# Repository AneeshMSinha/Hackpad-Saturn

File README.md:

# Hackpad-Saturn
My repository for Hack club, blueprint hackpad, called Saturn
This was an interesting and challenging project, was my first timee learning how to use Kicad and KMK.
## PCB
| Schematic | PCB |
|----------|----------|
|   | |
## Case

## Bill of materials

- 1 XIAO RP 2040 DIP
- 1 EC11 Rotary Encoder
- 1 SSD1306-0.91-OLED
- 1 PCB (black)
- 11 Cherry MX switches
- 11 Keycaps
- 12 DO-35 Diodes
- 1 3D printed case

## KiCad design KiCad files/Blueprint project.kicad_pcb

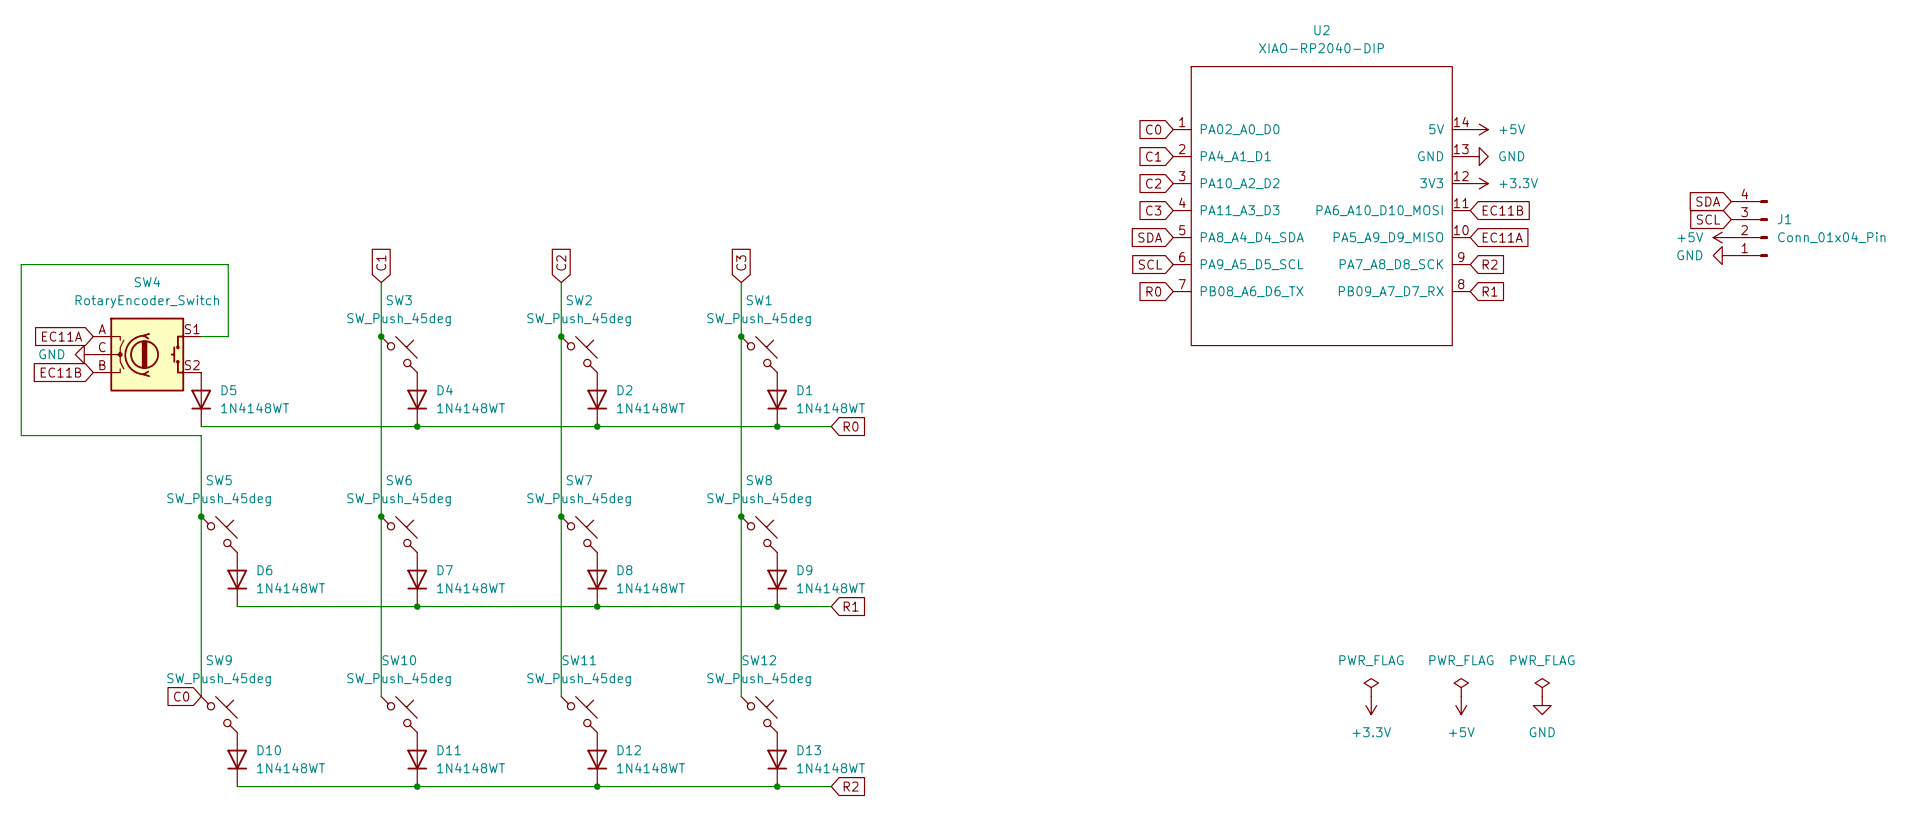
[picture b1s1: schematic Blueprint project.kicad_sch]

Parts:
D1, D2, D4, D5, D6, D7, D8, D9, D10, D11, D12, D13: 1N4148WT; D_DO-35_SOD27_P7.62mm_Horizontal
J1: Conn_01x04_Pin; SSD1306-0.91-OLED-4pin-128x32
SW1, SW2, SW3, SW5, SW6, SW7, SW8, SW9, SW10, SW11, SW12: SW_Push_45deg; SW_Cherry_MX_1.00u_PCB
SW4: RotaryEncoder_Switch; RotaryEncoder_Alps_EC11E-Switch_Vertical_H20mm
U2: XIAO-RP2040-DIP

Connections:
+3.3V: U2.12 (3V3)
+5V: J1.2, U2.14 (5V)
C0: SW4.S1, SW5.1, SW9.1, U2.1 (PA02_A0_D0)
C1: SW3.1, SW6.1, SW10.1, U2.2 (PA4_A1_D1)
C2: SW2.1, SW7.1, SW11.1, U2.3 (PA10_A2_D2)
C3: SW1.1, SW8.1, SW12.1, U2.4 (PA11_A3_D3)
EC11A: SW4.A, U2.10 (PA5_A9_D9_MISO)
EC11B: SW4.B, U2.11 (PA6_A10_D10_MOSI)
GND: J1.1, SW4.C, U2.13 (GND)
unnamed: D1.2 (A), SW1.2
unnamed: D2.2 (A), SW2.2
unnamed: D4.2 (A), SW3.2
unnamed: D5.2 (A), SW4.S2
unnamed: D6.2 (A), SW5.2
unnamed: D7.2 (A), SW6.2
unnamed: D8.2 (A), SW7.2
unnamed: D9.2 (A), SW8.2
unnamed: D10.2 (A), SW9.2
unnamed: D11.2 (A), SW10.2
unnamed: D12.2 (A), SW11.2
unnamed: D13.2 (A), SW12.2
R0: D1.1 (K), D2.1 (K), D4.1 (K), D5.1 (K), U2.7 (PB08_A6_D6_TX)
R1: D6.1 (K), D7.1 (K), D8.1 (K), D9.1 (K), U2.8 (PB09_A7_D7_RX)
R2: D10.1 (K), D11.1 (K), D12.1 (K), D13.1 (K), U2.9 (PA7_A8_D8_SCK)
SCL: J1.3, U2.6 (PA9_A5_D5_SCL)
SDA: J1.4, U2.5 (PA8_A4_D4_SDA)

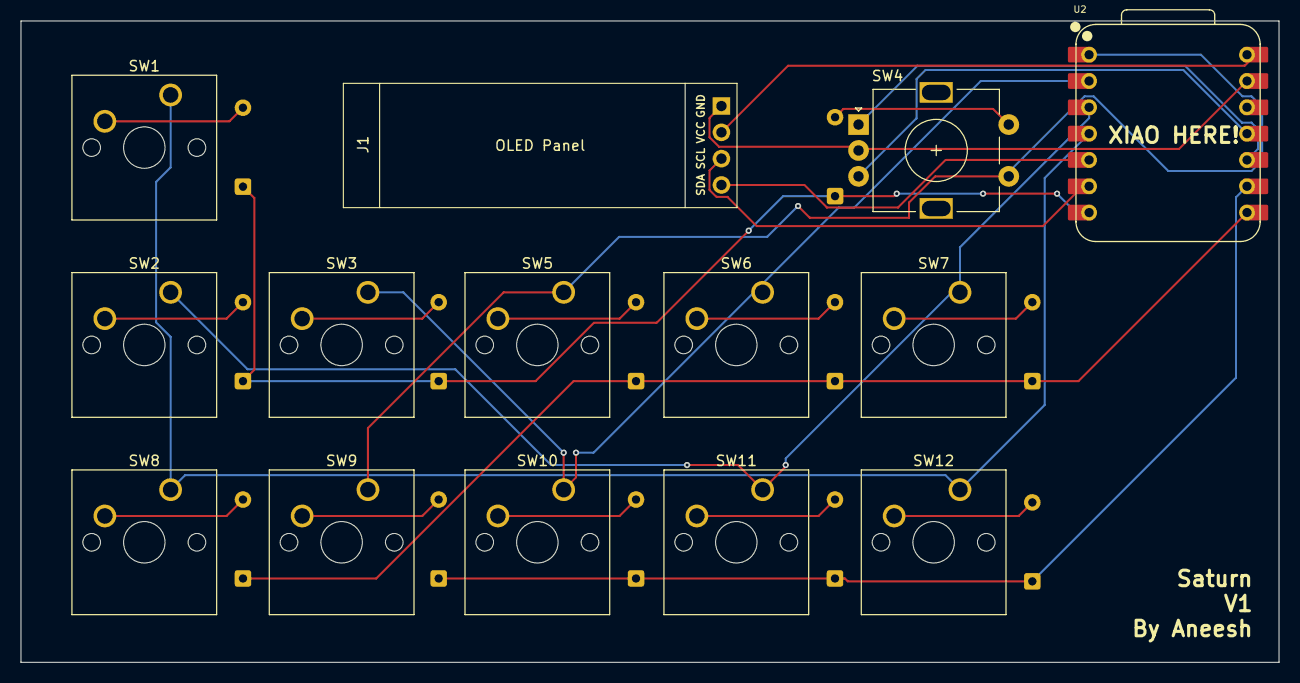
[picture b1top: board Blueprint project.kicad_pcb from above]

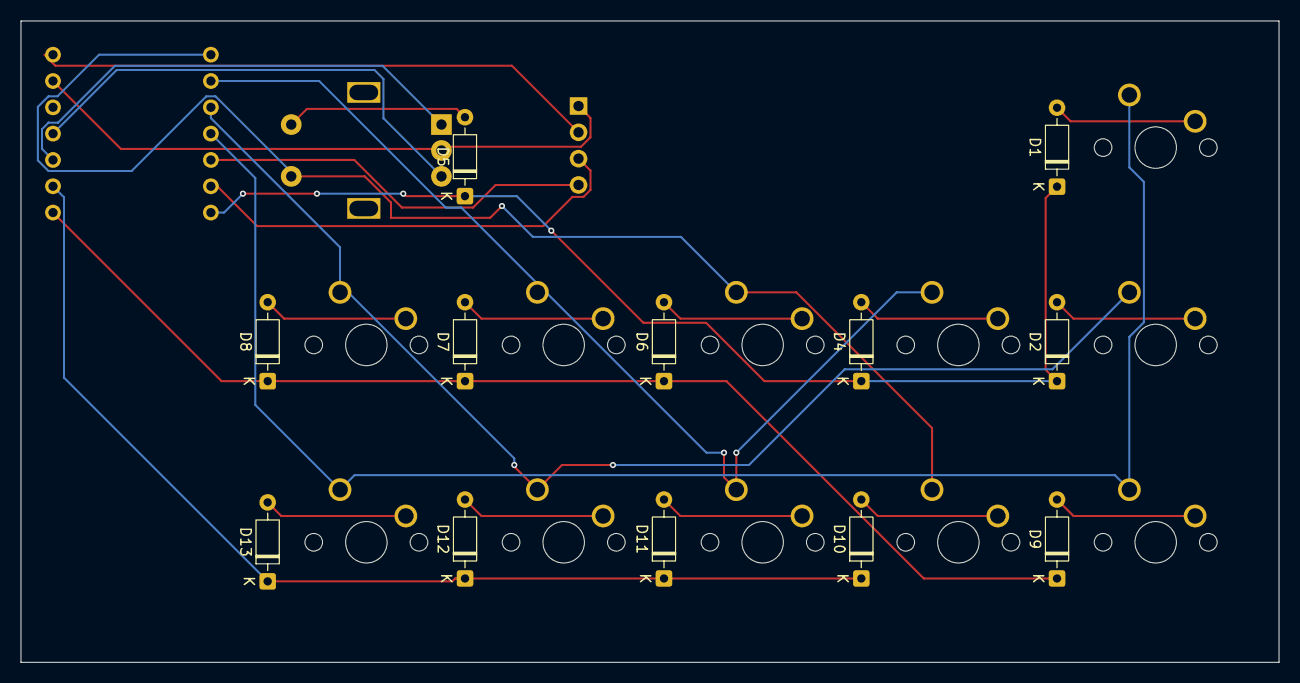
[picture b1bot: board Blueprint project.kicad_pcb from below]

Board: 2 copper layers, 121.4 x 61.9 mm, 26 parts (12 on the bottom side), 25 nets.
